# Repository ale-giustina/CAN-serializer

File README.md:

# CAN Serializer

A simple board that can be used to read up to 3 FDCAN bus lines using three filtered MCP2562FD with toggleable 120ohm termination resistors. Everything is hooked up to a STM32G473CCTx that is then hooked up to a USB-C receptacle. 

The board also features a USART interface, an SPI interface and an I2C interface for casual sensor debugging.

To connect to the can line a 1848943 1803329 PHOENIX CONNECTORS connector pair has been choosed for ease of operability.

A sample .ioc has been provided for the CUBEMX configuration.

# Board images

# V1.0 Assembled images

Firmware for the board can be found in the [CAN Serializer Firmware](https://github.com/ale-giustina/CAN-serializer-sw) repository.

# Warning
The BOOT0 pin has been overriden due to the presence of 3 FDCAN transceivers. This means that the board will not boot correctly. Before programming one needs to set the correct register through the SWD interface to ignore the BOOT0 pin.

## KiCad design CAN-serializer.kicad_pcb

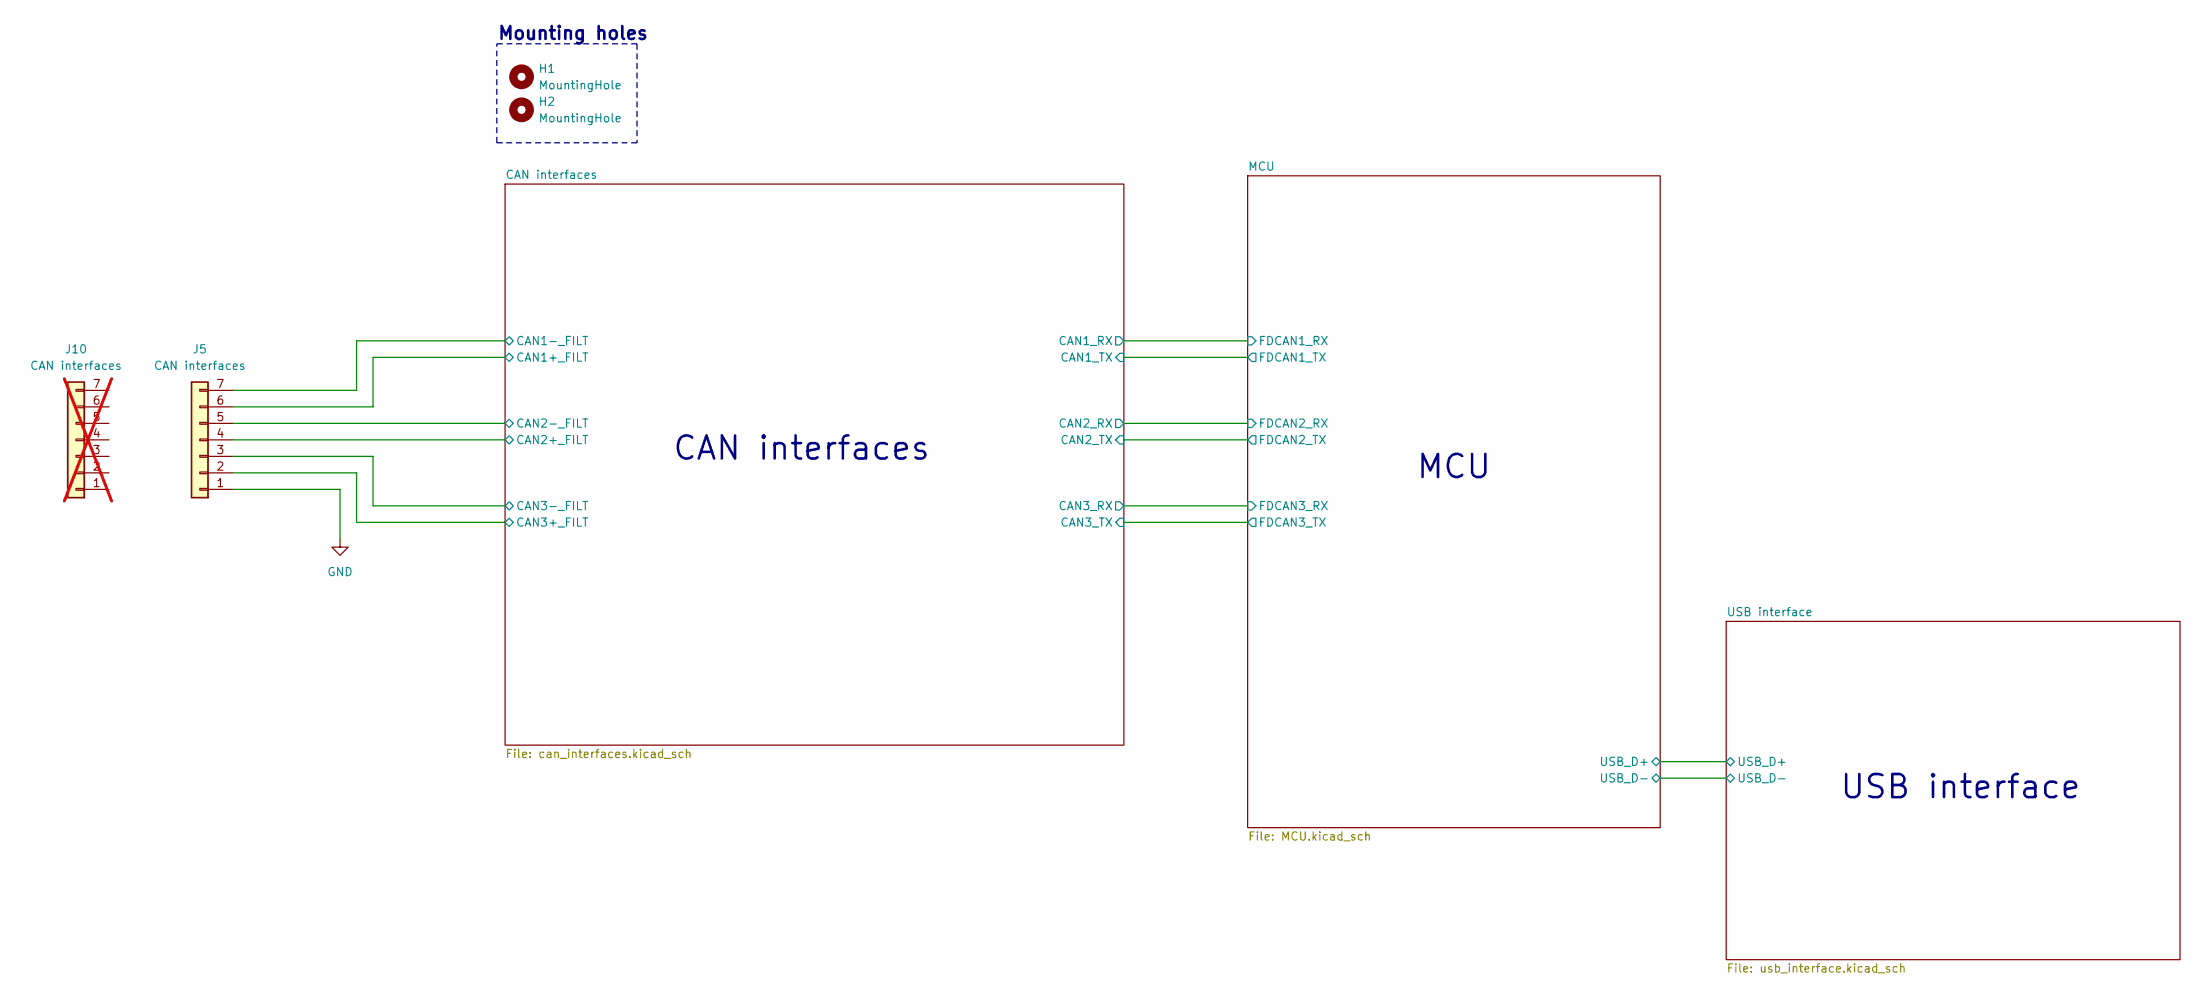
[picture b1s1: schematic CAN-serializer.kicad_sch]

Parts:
H1, H2: MountingHole; MountingHole_2.2mm_M2_ISO14580
J5: CAN interfaces; SHDRRA7W83P0X381_1X7_2806X920X825P; MOUSER PN 651-1803329
J10: CAN interfaces; 651-1848943; MOUSER PN 651-1848943; LCSC Part # 651-1848943; not fitted

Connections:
/CAN interfaces/CAN1+_FILT: J5.6; also elsewhere on the board
/CAN interfaces/CAN1-_FILT: J5.7; also elsewhere on the board
/CAN interfaces/CAN2+_FILT: J5.4; also elsewhere on the board
/CAN interfaces/CAN2-_FILT: J5.5; also elsewhere on the board
/CAN interfaces/CAN3+_FILT: J5.2; also elsewhere on the board
/CAN interfaces/CAN3-_FILT: J5.3; also elsewhere on the board
GND: J5.1; also elsewhere on the board

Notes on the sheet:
Mounting holes
USB interface
CAN interfaces
MCU

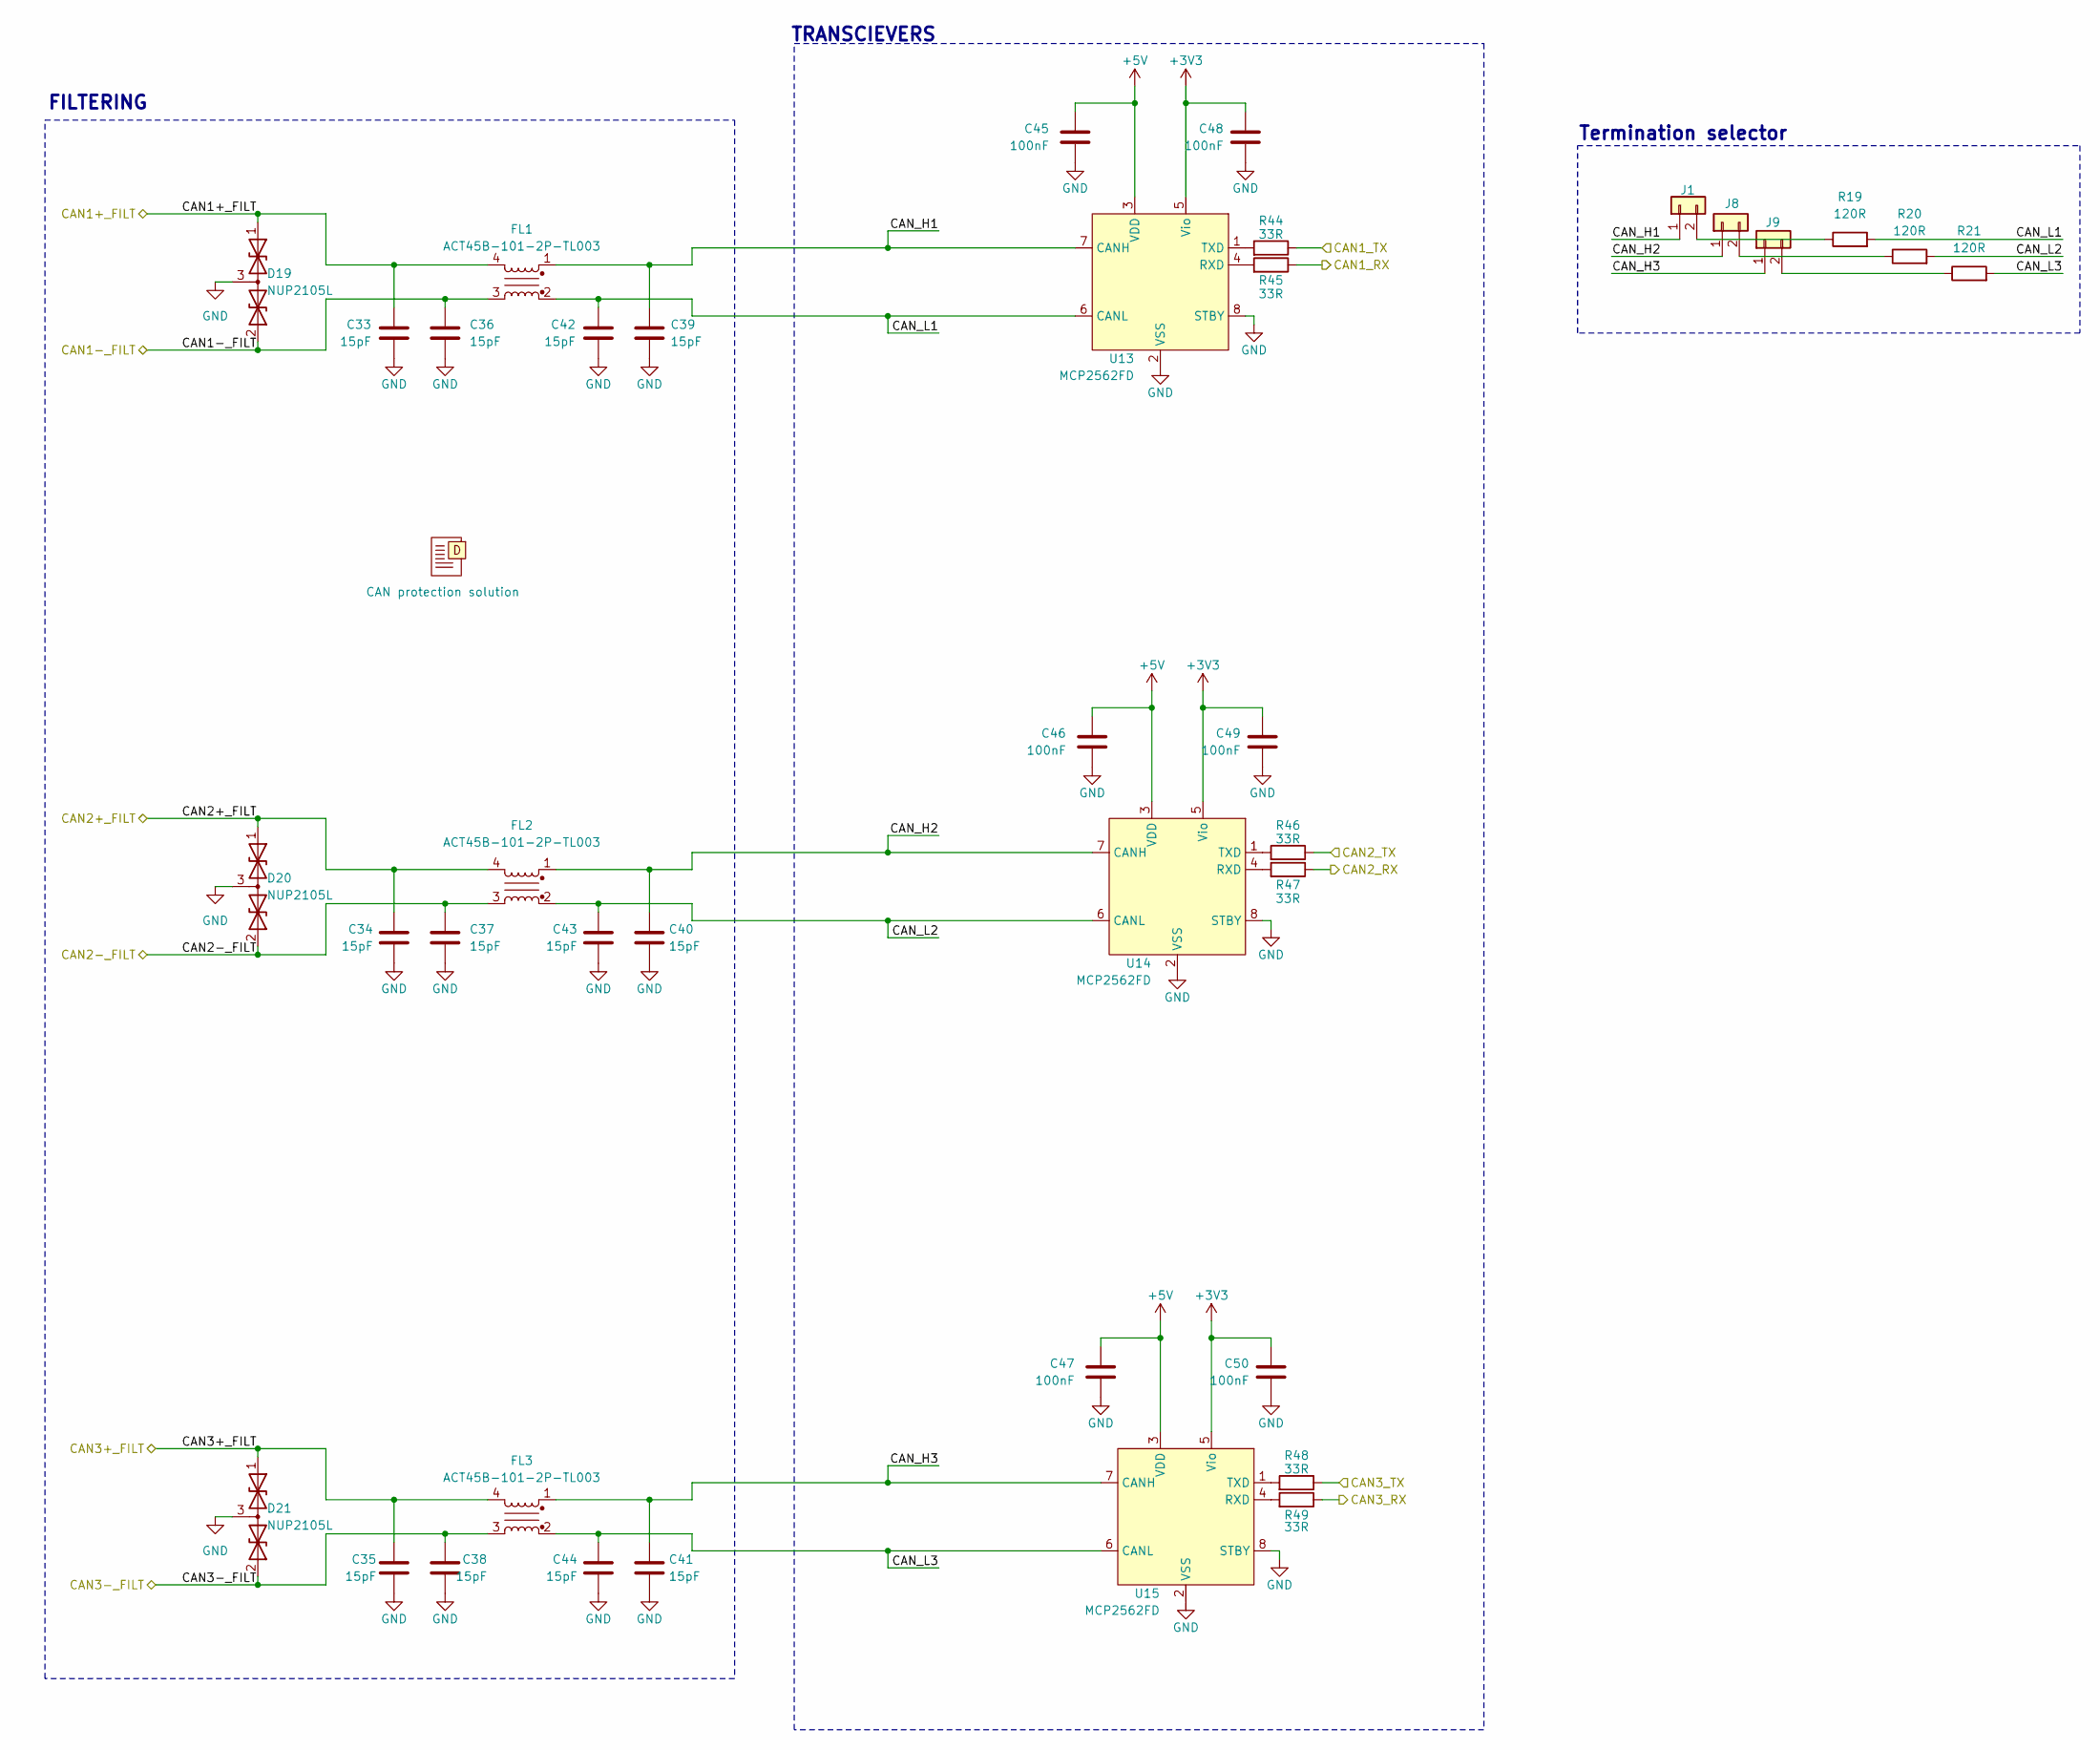
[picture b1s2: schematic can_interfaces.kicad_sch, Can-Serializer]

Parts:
C33, C34, C35, C36, C37, C38, C39, C40, C41, C42, C43, C44: 15pF; C_0603_1608Metric_Pad1.08x0.95mm_HandSolder; MOUSER PN 581-06031U150FAT2A; LCSC Part # C1644
C45, C46, C47, C48, C49, C50: 100nF; C_0603_1608Metric_Pad1.08x0.95mm_HandSolder; MOUSER PN 963-MAJCU168BB7104KT; LCSC Part # C14663
D19, D20, D21: NUP2105L; SOT-23; MOUSER PN 637-NUP2105L; LCSC Part # C284104
D22: CAN protection solution
FL1, FL2, FL3: ACT45B-101-2P-TL003; ACT45B-xxx-2P-TL003; MOUSER PN 810-ACT45B1012PTL003; LCSC Part # C88056
J1, J8, J9: Conn_01x02; PinHeader_1x02_P2.00mm_Vertical; LCSC Part # C376075
R19, R20, R21: 120R; R_0603_1608Metric_Pad0.98x0.95mm_HandSolder; MOUSER PN 652-CR0603-JW-121ELF; LCSC Part # C22787
R44, R45, R46, R47, R48, R49: 33R; R_0603_1608Metric_Pad0.98x0.95mm_HandSolder; MOUSER PN 603-AF0603JR-0733RL; LCSC Part # C23140
U13, U14, U15: MCP2562FD; SOIC-8_3.9x4.9mm_P1.27mm; MOUSER PN 579-MCP2562FD-H/SN; LCSC Part # C511335

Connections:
+3V3: C48.1, C49.1, C50.1, U13.5 (Vio), U14.5 (Vio), U15.5 (Vio); also elsewhere on the board
+5V: C45.1, C46.1, C47.1, U13.3 (VDD), U14.3 (VDD), U15.3 (VDD); also elsewhere on the board
/CAN interfaces/CAN1+_FILT: C33.1, D19.1 (A1), FL1.4; also elsewhere on the board
/CAN interfaces/CAN1-_FILT: C36.1, D19.2 (A2), FL1.3; also elsewhere on the board
/CAN interfaces/CAN1_RX: R45.1; also elsewhere on the board
/CAN interfaces/CAN1_TX: R44.1; also elsewhere on the board
/CAN interfaces/CAN2+_FILT: C34.1, D20.1 (A1), FL2.4; also elsewhere on the board
/CAN interfaces/CAN2-_FILT: C37.1, D20.2 (A2), FL2.3; also elsewhere on the board
/CAN interfaces/CAN2_RX: R47.1; also elsewhere on the board
/CAN interfaces/CAN2_TX: R46.1; also elsewhere on the board
/CAN interfaces/CAN3+_FILT: C35.1, D21.1 (A1), FL3.4; also elsewhere on the board
/CAN interfaces/CAN3-_FILT: C38.1, D21.2 (A2), FL3.3; also elsewhere on the board
/CAN interfaces/CAN3_RX: R49.1; also elsewhere on the board
/CAN interfaces/CAN3_TX: R48.1; also elsewhere on the board
/CAN interfaces/CAN_H1: C39.1, FL1.1, J1.1, U13.7 (CANH)
/CAN interfaces/CAN_H2: C40.1, FL2.1, J8.1, U14.7 (CANH)
/CAN interfaces/CAN_H3: C41.1, FL3.1, J9.1, U15.7 (CANH)
/CAN interfaces/CAN_L1: C42.1, FL1.2, R19.2, U13.6 (CANL)
/CAN interfaces/CAN_L2: C43.1, FL2.2, R20.2, U14.6 (CANL)
/CAN interfaces/CAN_L3: C44.1, FL3.2, R21.2, U15.6 (CANL)
GND: C33.2, C34.2, C35.2, C36.2, C37.2, C38.2, C39.2, C40.2, C41.2, C42.2, C43.2, C44.2, C45.2, C46.2, C47.2, C48.2, C49.2, C50.2, D19.3 (common), D20.3 (common), D21.3 (common), U13.2 (VSS), U13.8 (STBY), U14.2 (VSS), U14.8 (STBY), U15.2 (VSS), U15.8 (STBY); also elsewhere on the board
unnamed: J1.2, R19.1
unnamed: J8.2, R20.1
unnamed: J9.2, R21.1
unnamed: R45.2, U13.4 (RXD)
unnamed: R44.2, U13.1 (TXD)
unnamed: R47.2, U14.4 (RXD)
unnamed: R46.2, U14.1 (TXD)
unnamed: R49.2, U15.4 (RXD)
unnamed: R48.2, U15.1 (TXD)

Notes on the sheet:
TRANSCIEVERS
FILTERING
Termination selector

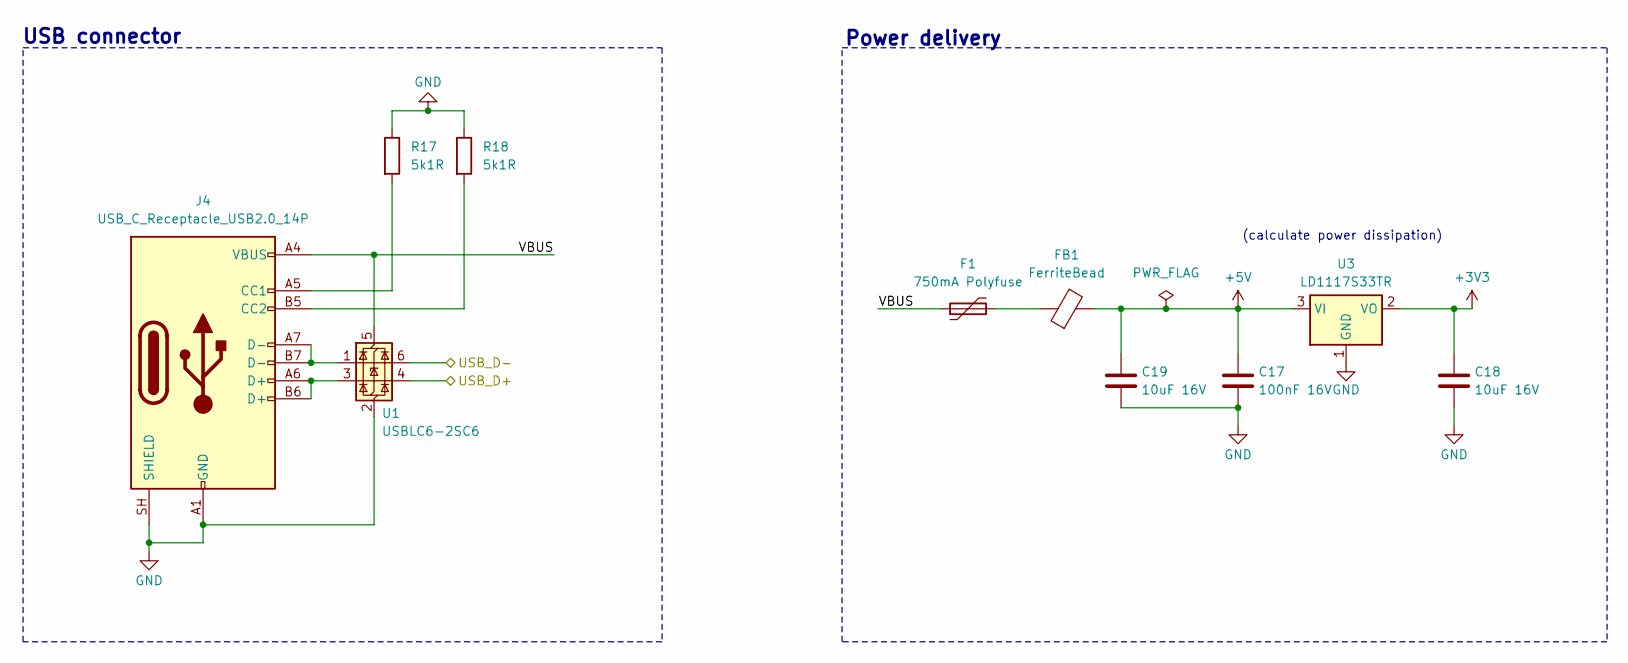
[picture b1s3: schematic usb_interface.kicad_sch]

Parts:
C17: 100nF 16V; C_0805_2012Metric_Pad1.18x1.45mm_HandSolder; MOUSER PN 581-0805YC104M4T2A; LCSC Part # C49678
C18, C19: 10uF 16V; C_0805_2012Metric_Pad1.18x1.45mm_HandSolder; MOUSER PN 603-CC0805MKX77BB106; LCSC Part # C15850
F1: 750mA Polyfuse; Fuse_1206_3216Metric_Pad1.42x1.75mm_HandSolder; MOUSER PN 576-1206L075SLYR; LCSC Part # C7542952
FB1: FerriteBead; L_0603_1608Metric; MOUSER PN 81-BLM18PG221SN1D; LCSC Part # C80165
J4: USB_C_Receptacle_USB2.0_14P; USB_C_Receptacle_XKB_U262-16XN-4BVC11; MOUSER PN 640-USB4105-GF-A; LCSC Part # C319148
R17, R18: 5k1R; R_0603_1608Metric_Pad0.98x0.95mm_HandSolder; MOUSER PN 603-RE0603FRE075K1L; LCSC Part # C14677
U1: USBLC6-2SC6; SOT-23-6; MOUSER PN 511-USBLC6-2SC6; LCSC Part # C2827654
U3: LD1117S33TR; SOT-223-3_TabPin2; MOUSER PN 511-LD1117S33; LCSC Part # C86781

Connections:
+3V3: C18.1, U3.2 (VO); also elsewhere on the board
+5V: C17.1, C19.1, FB1.2, U3.3 (VI); also elsewhere on the board
/MCU/USB_D+: U1.4 (I/O2); also elsewhere on the board
/MCU/USB_D-: U1.6 (I/O1); also elsewhere on the board
/USB interface/VBUS: F1.1, J4.A4 (VBUS), J4.A9 (VBUS), J4.B4 (VBUS), J4.B9 (VBUS), U1.5 (VBUS)
GND: C17.2, C18.2, C19.2, J4.A1 (GND), J4.A12 (GND), J4.B1 (GND), J4.B12 (GND), J4.SH (SHIELD), R17.1, R18.1, U1.2 (GND), U3.1 (GND); also elsewhere on the board
unnamed: F1.2, FB1.1
unnamed: J4.A5 (CC1), R17.2
unnamed: J4.B5 (CC2), R18.2
unnamed: J4.A6 (D+), J4.B6 (D+), U1.3 (I/O2)
unnamed: J4.A7 (D-), J4.B7 (D-), U1.1 (I/O1)

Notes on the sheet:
(calculate power dissipation)
USB connector
Power delivery

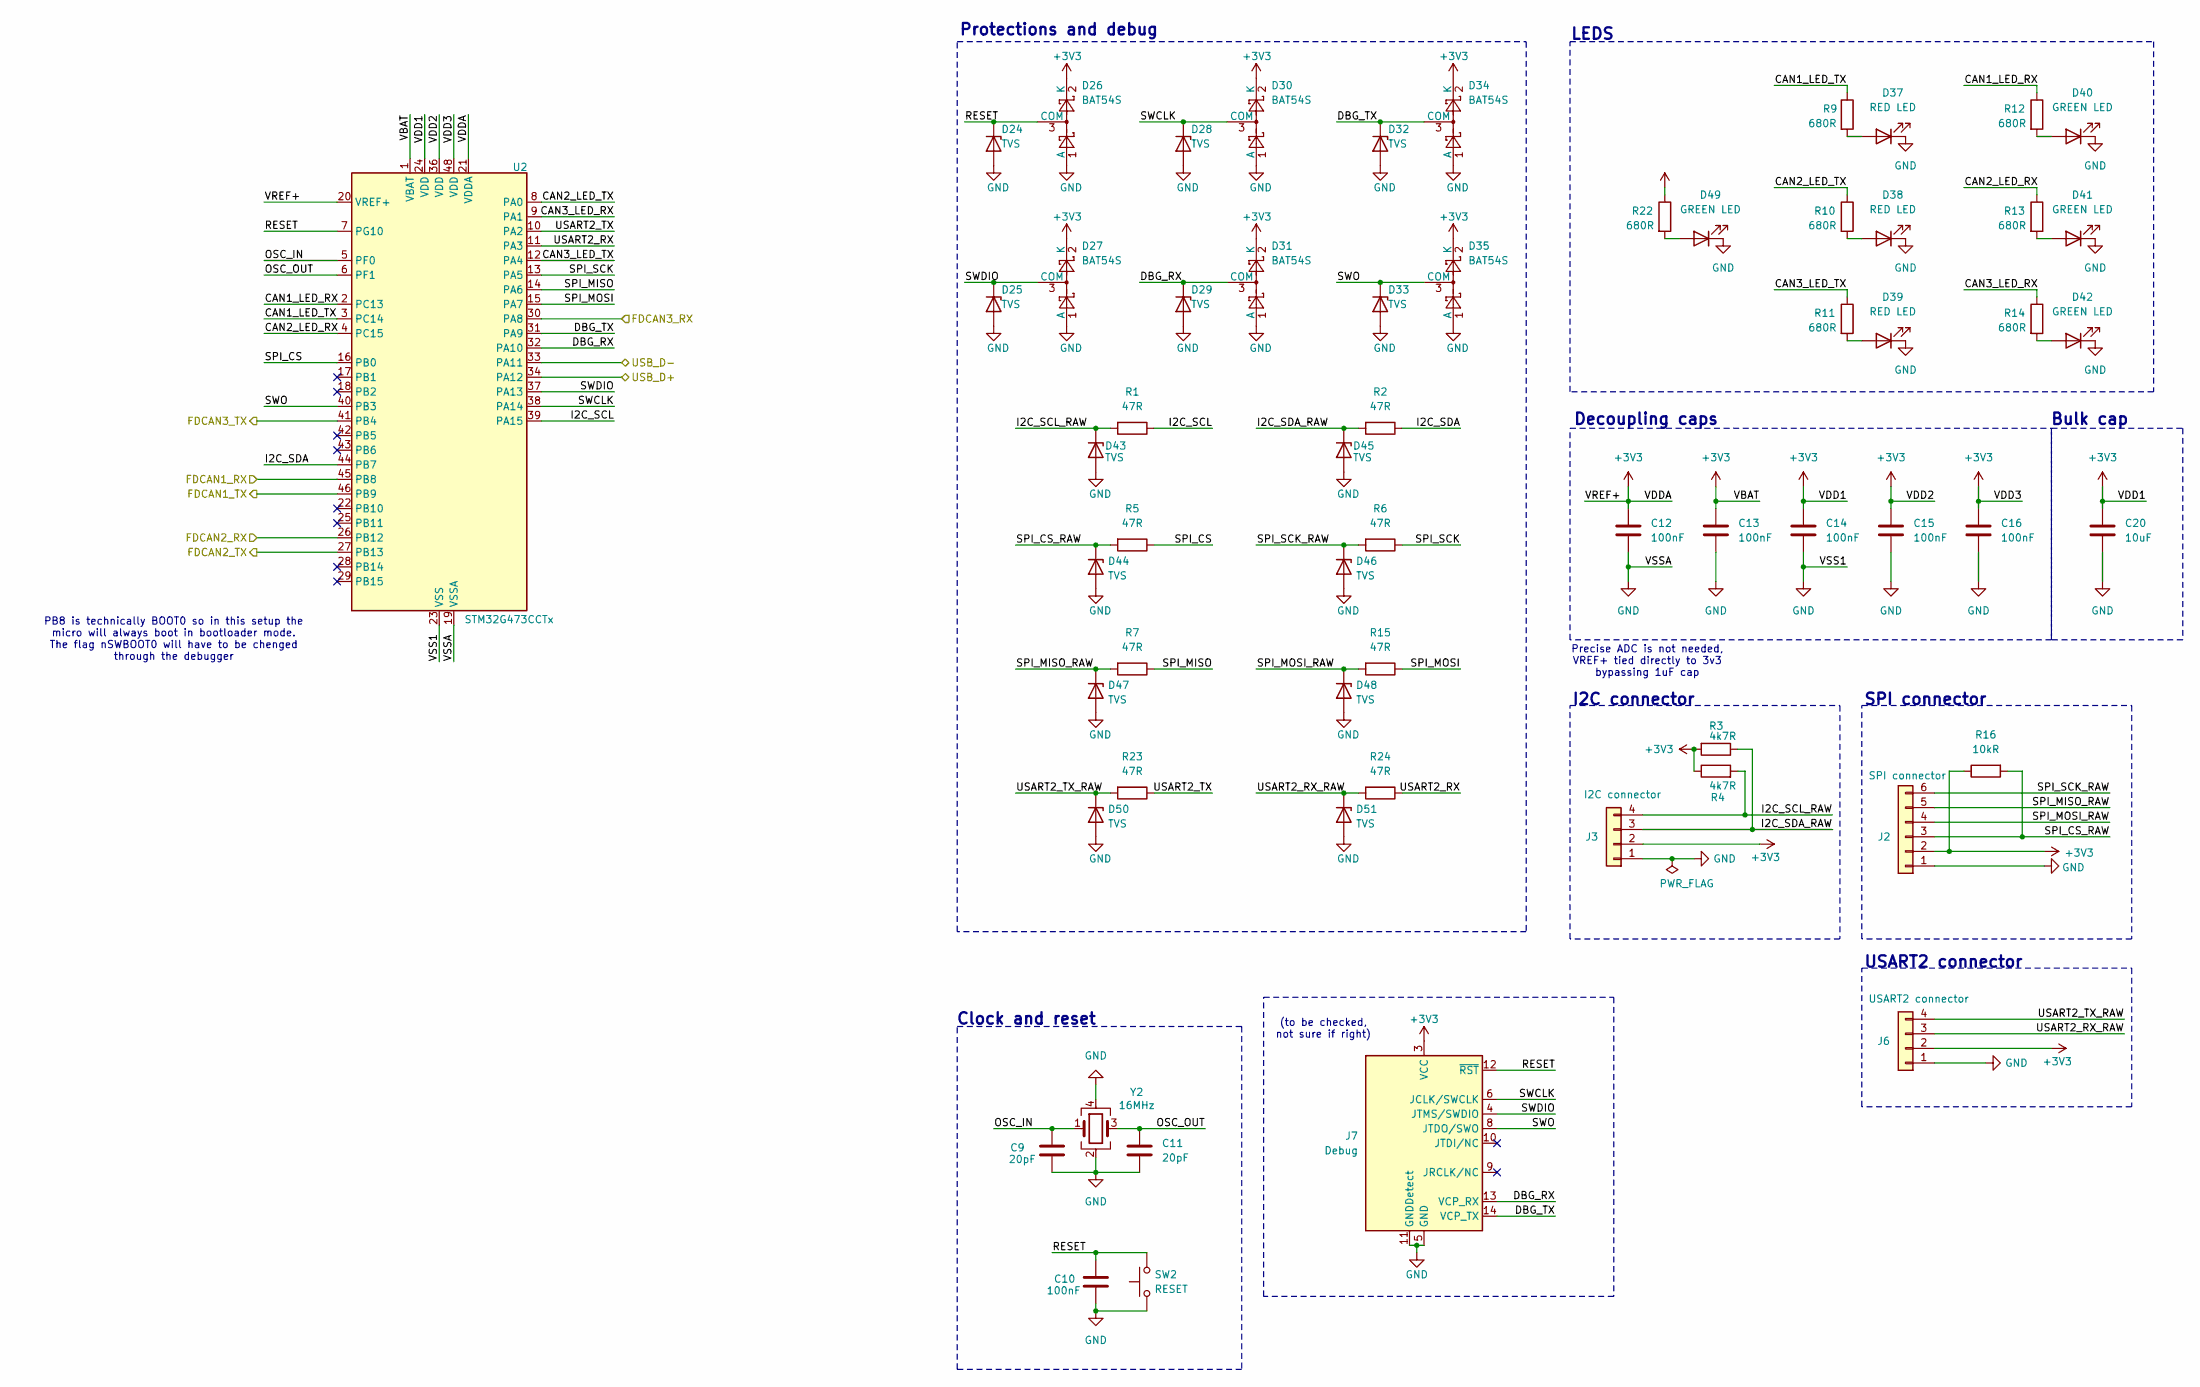
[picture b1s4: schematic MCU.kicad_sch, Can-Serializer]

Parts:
C9, C11: 20pF; C_0603_1608Metric_Pad1.08x0.95mm_HandSolder; MOUSER PN 581-06035A200GAT2A; LCSC Part # C1648
C10, C12, C13, C14, C15, C16: 100nF; C_0603_1608Metric_Pad1.08x0.95mm_HandSolder; MOUSER PN 963-MAJCU168BB7104KT; LCSC Part # C14663
C20: 10uF; C_0603_1608Metric_Pad1.08x0.95mm_HandSolder; MOUSER PN 581-KGM15CR51C106KT; LCSC Part # C19702
D24, D25, D28, D29, D32, D33, D43, D44, D45, D46, D47, D48, D50, D51: TVS; D_SOD-523; MOUSER PN 750-CPDH3V3UP; LCSC Part # C77807
D26, D27, D30, D31, D34, D35: BAT54S; SOT-23; MOUSER PN 863-SBAT54SLT1G; LCSC Part # C7420333
D37, D38, D39: RED LED; LED_0603_1608Metric_Pad1.05x0.95mm_HandSolder; MOUSER PN 604-APT1608SURCK-AMT; LCSC Part # C965799
D40, D41, D42, D49: GREEN LED; LED_0603_1608Metric_Pad1.05x0.95mm_HandSolder; MOUSER PN 720-Q65113A7469; LCSC Part # C7496818
J2: SPI connector; PinHeader_1x06_P2.54mm_Vertical; LCSC Part # C37208
J3: I2C connector; PinHeader_1x04_P2.54mm_Vertical; LCSC Part # C124378
J6: USART2 connector; PinHeader_1x04_P2.54mm_Vertical; LCSC Part # C124378
J7: Debug; SAMTEC_FTSH-107-01-L-DV-K-TR; MOUSER PN 200-FTSH10701LDVKTR; LCSC Part # C22074484
R1, R2, R5, R6, R7, R15, R23, R24: 47R; R_0603_1608Metric_Pad0.98x0.95mm_HandSolder; MOUSER PN 603-TR0603KR-0747RL; LCSC Part # C23182
R3, R4: 4k7R; R_0603_1608Metric_Pad0.98x0.95mm_HandSolder; MOUSER PN 603-AR0603JR-074K7L; LCSC Part # C99782
R9, R10, R11, R12, R13, R14, R22: 680R; R_0603_1608Metric_Pad0.98x0.95mm_HandSolder; MOUSER PN 667-ERA-3APB681V; LCSC Part # C23228
R16: 10kR; R_0603_1608Metric_Pad0.98x0.95mm_HandSolder; MOUSER PN 594-MCT06030D1002BPW; LCSC Part # C25804
SW2: RESET; SW_SPST_FSMSM; MOUSER PN 506-FSMSM
U2: STM32G473CCTx; LQFP-48_7x7mm_P0.5mm; MOUSER PN 511-STM32G473CCT3
Y2: 16MHz; Crystal_SMD_EuroQuartz_MT-4Pin_3.2x2.5mm; MOUSER PN 520-160-18-33-AENTR3; LCSC Part # C6190540

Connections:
+3V3: C12.1, C13.1, C14.1, C15.1, C16.1, C20.1, D26.2 (K), D27.2 (K), D30.2 (K), D31.2 (K), D34.2 (K), D35.2 (K), J2.2, J3.2, J6.2, J7.3 (VCC), R3.2, R4.1, R16.1, R22.1, U2.1 (VBAT), U2.20 (VREF+), U2.21 (VDDA), U2.24 (VDD), U2.36 (VDD), U2.48 (VDD); also elsewhere on the board
/CAN interfaces/CAN1_RX: U2.45 (PB8); also elsewhere on the board
/CAN interfaces/CAN1_TX: U2.46 (PB9); also elsewhere on the board
/CAN interfaces/CAN2_RX: U2.26 (PB12); also elsewhere on the board
/CAN interfaces/CAN2_TX: U2.27 (PB13); also elsewhere on the board
/CAN interfaces/CAN3_RX: U2.30 (PA8); also elsewhere on the board
/CAN interfaces/CAN3_TX: U2.41 (PB4); also elsewhere on the board
/MCU/CAN1_LED_RX: R12.1, U2.2 (PC13)
/MCU/CAN1_LED_TX: R9.1, U2.3 (PC14)
/MCU/CAN2_LED_RX: R13.1, U2.4 (PC15)
/MCU/CAN2_LED_TX: R10.1, U2.8 (PA0)
/MCU/CAN3_LED_RX: R14.1, U2.9 (PA1)
/MCU/CAN3_LED_TX: R11.1, U2.12 (PA4)
/MCU/DBG_RX: D29.1 (K), D31.3 (COM), J7.13 (VCP_RX), U2.32 (PA10)
/MCU/DBG_TX: D32.1 (K), D34.3 (COM), J7.14 (VCP_TX), U2.31 (PA9)
/MCU/I2C_SCL: R1.1, U2.39 (PA15)
/MCU/I2C_SCL_RAW: D43.1 (K), J3.4, R1.2, R4.2
/MCU/I2C_SDA: R2.1, U2.44 (PB7)
/MCU/I2C_SDA_RAW: D45.1 (K), J3.3, R2.2, R3.1
/MCU/OSC_IN: C9.1, U2.5 (PF0), Y2.1
/MCU/OSC_OUT: C11.1, U2.6 (PF1), Y2.3
/MCU/RESET: C10.1, D24.1 (K), D26.3 (COM), J7.12 (~RST), SW2.2, U2.7 (PG10)
/MCU/SPI_CS: R5.1, U2.16 (PB0)
/MCU/SPI_CS_RAW: D44.1 (K), J2.3, R5.2, R16.2
/MCU/SPI_MISO: R7.1, U2.14 (PA6)
/MCU/SPI_MISO_RAW: D47.1 (K), J2.5, R7.2
/MCU/SPI_MOSI: R15.1, U2.15 (PA7)
/MCU/SPI_MOSI_RAW: D48.1 (K), J2.4, R15.2
/MCU/SPI_SCK: R6.1, U2.13 (PA5)
/MCU/SPI_SCK_RAW: D46.1 (K), J2.6, R6.2
/MCU/SWCLK: D28.1 (K), D30.3 (COM), J7.6 (JCLK/SWCLK), U2.38 (PA14)
/MCU/SWDIO: D25.1 (K), D27.3 (COM), J7.4 (JTMS/SWDIO), U2.37 (PA13)
/MCU/SWO: D33.1 (K), D35.3 (COM), J7.8 (JTDO/SWO), U2.40 (PB3)
/MCU/USART2_RX: R24.1, U2.11 (PA3)
/MCU/USART2_RX_RAW: D51.1 (K), J6.3, R24.2
/MCU/USART2_TX: R23.1, U2.10 (PA2)
/MCU/USART2_TX_RAW: D50.1 (K), J6.4, R23.2
/MCU/USB_D+: U2.34 (PA12); also elsewhere on the board
/MCU/USB_D-: U2.33 (PA11); also elsewhere on the board
GND: C9.2, C10.2, C11.2, C12.2, C13.2, C14.2, C15.2, C16.2, C20.2, D24.2 (A), D25.2 (A), D26.1 (A), D27.1 (A), D28.2 (A), D29.2 (A), D30.1 (A), D31.1 (A), D32.2 (A), D33.2 (A), D34.1 (A), D35.1 (A), D37.1 (K), D38.1 (K), D39.1 (K), D40.1 (K), D41.1 (K), D42.1 (K), D43.2 (A), D44.2 (A), D45.2 (A), D46.2 (A), D47.2 (A), D48.2 (A), D49.1 (K), D50.2 (A), D51.2 (A), J2.1, J3.1, J6.1, J7.5 (GND), J7.7 (GND), J7.11 (GNDDetect), SW2.1, U2.19 (VSSA), U2.23 (VSS), U2.35 (VSS), U2.47 (VSS), Y2.2 (G), Y2.4; also elsewhere on the board
unnamed: D37.2 (A), R9.2
unnamed: D38.2 (A), R10.2
unnamed: D39.2 (A), R11.2
unnamed: D40.2 (A), R12.2
unnamed: D41.2 (A), R13.2
unnamed: D42.2 (A), R14.2
unnamed: D49.2 (A), R22.2

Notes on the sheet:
SPI connector
Protections and debug
USART2 connector
LEDS
Decoupling caps
Clock and reset
I2C connector
(to be checked, not sure if right)
PB8 is technically BOOT0 so in this setup the micro will always boot in bootloader mode. The flag nSWBOOT0 will have to be chenged through the debugger
Precise ADC is not needed, VREF+ tied directly to 3v3 bypassing 1uF cap
Bulk cap

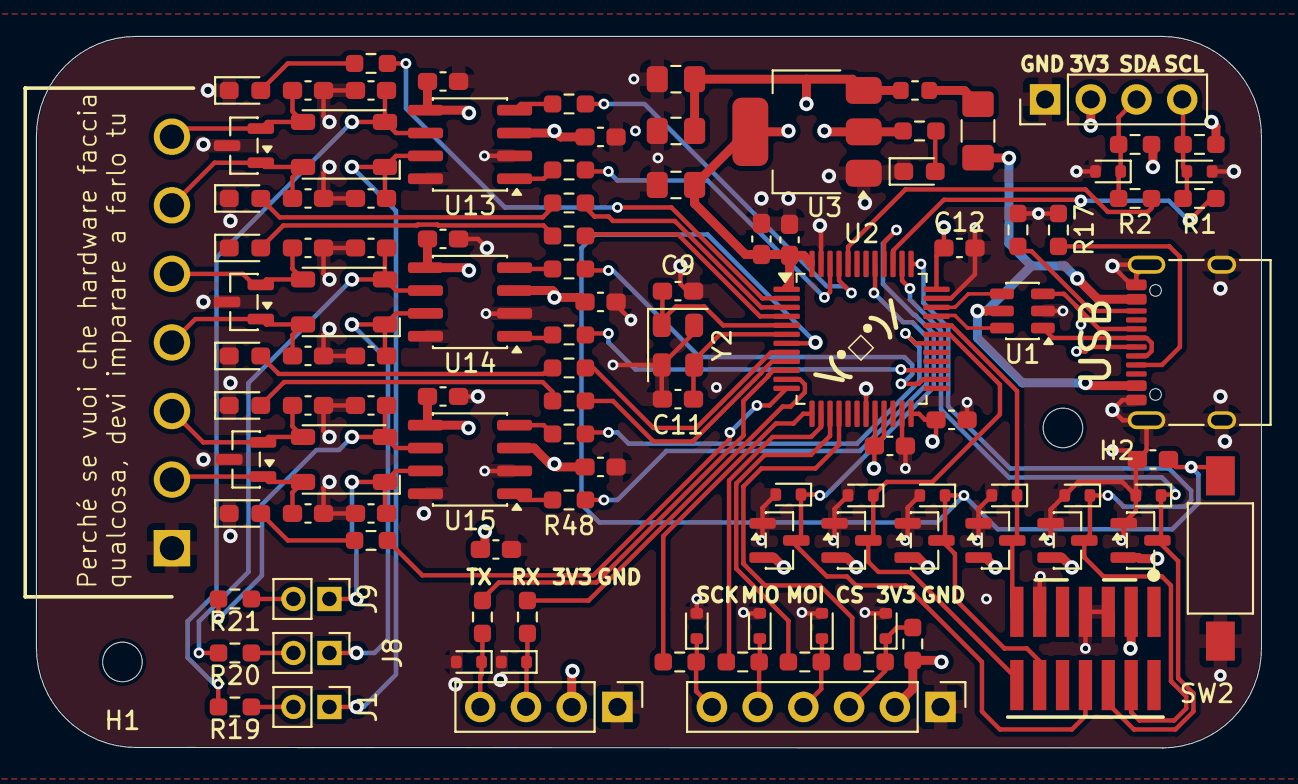
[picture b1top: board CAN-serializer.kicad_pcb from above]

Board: 4 copper layers, 68.1 x 39.5 mm, 113 parts (0 on the bottom side), 75 nets.

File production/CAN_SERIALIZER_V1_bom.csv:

Designator,Footprint,Quantity,Value,LCSC Part #
"C10, C12, C13, C14, C15, C16, C45, C46, C47, C48, C49, C50",0603,12,100nF,C14663
"C11, C9",0603,2,20pF,C1648
C17,0805,1,100nF 16V,C49678
"C18, C19",0805,2,10uF 16V,C15850
C20,0603,1,10uF,C19702
"C33, C34, C35, C36, C37, C38, C39, C40, C41, C42, C43, C44",0603,12,15pF,C1644
"D19, D20, D21",SOT-23,3,NUP2105L,C284104
"D24, D25, D28, D29, D32, D33, D43, D44, D45, D46, D47, D48, D50, D51",D_SOD-523,14,TVS,C77807
"D26, D27, D30, D31, D34, D35",SOT-23,6,BAT54S,C7420333
"D37, D38, D39",0603,3,RED LED,C965799
"D40, D41, D42, D49",0603,4,GREEN LED,C7496818
F1,1206,1,750mA Polyfuse,C7542952
FB1,0603,1,FerriteBead,C80165
"FL1, FL2, FL3",ACT45B-xxx-2P-TL003,3,ACT45B-101-2P-TL003,C88056
"J1, J8, J9",PinHeader_1x02_P2.00mm_Vertical,3,Conn_01x02,C376075
J2,PinHeader_1x06_P2.54mm_Vertical,1,SPI connector,C37208
J3,PinHeader_1x04_P2.54mm_Vertical,1,I2C connector,C124378
J4,USB_C_Receptacle_XKB_U262-16XN-4BVC11,1,USB_C_Receptacle_USB2.0_14P,C319148
J5,SHDRRA7W83P0X381_1X7_2806X920X825P,1,CAN interfaces,
J6,PinHeader_1x04_P2.54mm_Vertical,1,USART2 connector,C124378
J7,SAMTEC_FTSH-107-01-L-DV-K-TR,1,Debug,C22074484
"R1, R15, R2, R23, R24, R5, R6, R7",0603,8,47R,C23182
"R10, R11, R12, R13, R14, R22, R9",0603,7,680R,C23228
R16,0603,1,10kR,C25804
"R17, R18",0603,2,5k1R,C14677
"R19, R20, R21",0603,3,120R,C22787
"R3, R4",0603,2,4k7R,C99782
"R44, R45, R46, R47, R48, R49",0603,6,33R,C23140
SW2,SW_SPST_FSMSM,1,RESET,
U1,SOT-23-6,1,USBLC6-2SC6,C2827654
"U13, U14, U15",SOIC-8_3.9x4.9mm_P1.27mm,3,MCP2562FD,C511335
U2,LQFP-48_7x7mm_P0.5mm,1,STM32G473CCTx,
U3,SOT-223-3_TabPin2,1,LD1117S33TR,C86781
Y2,Crystal_SMD_EuroQuartz_MT-4Pin_3.2x2.5mm,1,16MHz,C6190540

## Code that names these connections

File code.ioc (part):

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Mcu.Name=STM32G473C(B-C-E)Tx
Mcu.Package=LQFP48
Mcu.UserName=STM32G473CCTx
PA0.GPIOParameters=GPIO_Label
PA0.GPIO_Label=CAN2_LED_TX
PA0.Signal=GPIO_Output
PA1.GPIOParameters=GPIO_Label
PA1.GPIO_Label=CAN3_LED_RX
PA1.Signal=GPIO_Output
PA10.Mode=Asynchronous
PA10.Signal=USART1_RX
PA11.Mode=Device
PA11.Signal=USB_DM
PA12.Mode=Device
PA12.Signal=USB_DP
PA13.Mode=Trace_Asynchronous_SW
PA13.Signal=SYS_JTMS-SWDIO
PA14.Mode=Trace_Asynchronous_SW
PA14.Signal=SYS_JTCK-SWCLK
PA15.Mode=I2C
PA15.Signal=I2C1_SCL
PA2.Mode=Asynchronous
PA2.Signal=USART2_TX
PA3.Mode=Asynchronous
PA3.Signal=USART2_RX
PA4.GPIOParameters=GPIO_Label
PA4.GPIO_Label=CAN3_LED_TX
PA4.Signal=GPIO_Output
PA5.Mode=Full_Duplex_Master
PA5.Signal=SPI1_SCK
PA6.Mode=Full_Duplex_Master
PA6.Signal=SPI1_MISO
PA7.Mode=Full_Duplex_Master
PA7.Signal=SPI1_MOSI
PA8.Mode=FDCAN_Activate
PA8.Signal=FDCAN3_RX
PA9.Mode=Asynchronous
PA9.Signal=USART1_TX
PB0.GPIOParameters=GPIO_Label
PB0.GPIO_Label=SPI_CS
PB0.Signal=GPIO_Output
PB12.Mode=FDCAN_Activate
PB12.Signal=FDCAN2_RX
PB13.Mode=FDCAN_Activate
PB13.Signal=FDCAN2_TX
PB3.Mode=Trace_Asynchronous_SW
PB3.Signal=SYS_JTDO-SWO
PB4.Mode=FDCAN_Activate
PB4.Signal=FDCAN3_TX
PB7.Mode=I2C
PB7.Signal=I2C1_SDA
PB8-BOOT0.Mode=FDCAN_Activate
PB8-BOOT0.Signal=FDCAN1_RX
PB9.Mode=FDCAN_Activate
PB9.Signal=FDCAN1_TX
PC13.GPIOParameters=GPIO_Label
PC13.GPIO_Label=CAN1_LED_RX
PC13.Signal=GPIO_Output
PC14-OSC32_IN.GPIOParameters=GPIO_Label
PC14-OSC32_IN.GPIO_Label=CAN1_LED_TX
PC14-OSC32_IN.Signal=GPIO_Output
PC15-OSC32_OUT.GPIOParameters=GPIO_Label
PC15-OSC32_OUT.GPIO_Label=CAN2_LED_RX
PC15-OSC32_OUT.Signal=GPIO_Output
PF0-OSC_IN.Mode=HSE-External-Oscillator
PF0-OSC_IN.Signal=RCC_OSC_IN
PF1-OSC_OUT.Mode=HSE-External-Oscillator
PF1-OSC_OUT.Signal=RCC_OSC_OUT
RCC.HSE_VALUE=16000000
RCC.SYSCLKFreq_VALUE=168000000
RCC.SYSCLKSource=RCC_SYSCLKSOURCE_PLLCLK
board=custom
